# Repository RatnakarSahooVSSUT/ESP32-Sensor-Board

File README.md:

# ESP32-Sensor-Board

> A custom ESP32-C3 based sensor and embedded systems development board designed in KiCad 9.

<p align="center">
  <b>Custom ESP32-C3 Sensor & Embedded Systems Development Board</b>
</p>

---

## 📌 Overview

The **ESP32-Sensor-Board** is a custom embedded systems development board built around the **ESP32-C3** microcontroller.

The board integrates environmental sensing, sound sensing, USB connectivity, battery charging, power regulation, user-interface controls, and external expansion interfaces into a single compact PCB.

The complete hardware design was developed in **KiCad 9**, including schematic capture, hierarchical design, PCB layout, 3D visualization, custom libraries, DFM analysis, and manufacturing outputs.

---

## ✨ Key Features

- 🧠 ESP32-C3 based processing
- 🌡️ BME280 environmental sensor
- 🔊 On-board sound sensing
- 🔌 USB connectivity
- 🔋 Li-ion/Li-Po battery charging
- ⚡ On-board voltage regulation
- 💡 Power and charging indicators
- 🔘 Boot and reset buttons
- 📡 I2C interface
- 🚀 SPI interface
- 🔗 GPIO expansion
- 🧪 Dedicated test points
- 📦 Custom KiCad symbol and footprint libraries
- 🏭 Manufacturing-ready Gerber and drill files
- 📐 Hierarchical schematic design

---

# 🧩 Hardware Overview

| Component / Feature | Description |
|---|---|
| Microcontroller | ESP32-C3 |
| Environmental Sensor | BME280 |
| Sound Sensing | On-board sound sensing circuit |
| USB | USB connectivity |
| Power Input | USB / Rechargeable Battery |
| Battery Charging | Li-ion/Li-Po charging circuit |
| Regulation | On-board voltage regulation |
| Communication | I2C / SPI |
| Expansion | GPIO headers |
| Debugging | Test points |
| PCB Design | KiCad 9 |

---

# 📐 Schematic

The design follows a **hierarchical schematic structure**, separating the major functional blocks into dedicated schematic sheets.

## Complete Schematic

---

# 🌡️ Sensor Section

The sensor subsystem includes the **BME280 environmental sensor**.

### BME280

The BME280 provides digital measurements of:

- Temperature
- Relative Humidity
- Atmospheric Pressure

The sensor communicates with the ESP32-C3 through a digital interface.

### 🔊 Sound Sensing

An on-board sound sensing circuit is also included for detecting variations in ambient sound.

Potential applications include:

- Environmental monitoring
- Sound/activity detection
- IoT sensing
- Event-triggered applications

---

# ⚡ Power Management

The power subsystem manages the board's power input, battery charging, voltage regulation, and status indication.

The design includes:

- USB power input
- Rechargeable battery support
- Battery charging
- Voltage regulation
- Power-status indication
- Charging-status indication

---

# 🎛️ User Interface

The board provides several controls and indicators for development, debugging, and normal operation.

### User Interface Features

- Boot button
- Reset button
- Power indicator
- Charging indicators
- USB RX/TX indicators
- Status indicators

---

# 🖥️ PCB Design

The PCB was designed using **KiCad 9** with emphasis on:

- Compact component placement
- Organized routing
- Functional block separation
- Practical power distribution
- Accessible debugging points
- Clear silkscreen labeling
- External expansion
- Manufacturability

## PCB Layout

## 3D PCB View

---

# 🔌 Interfaces

## USB

USB connectivity is provided for:

- Power
- Programming
- Serial communication

## I2C

The I2C interface allows additional sensors and peripherals to be connected to the board.

## SPI

SPI connectivity is available for peripherals requiring higher-speed communication, such as displays, memory devices, and other external modules.

## GPIO

Additional GPIO pins are exposed through board headers for connecting external sensors, modules, and other peripherals.

---

# 🧪 Debugging & Test Points

Dedicated test points are provided across the board to make hardware bring-up, debugging, and signal verification easier.

These can be used with a:

- Multimeter
- Oscilloscope
- Logic analyzer
- Other debugging equipment

---

# 🏭 Manufacturing

Manufacturing files are provided in the:

**`ESP32_Gerbers/`**

directory.

The repository contains the generated **Gerber and drill files** required for PCB fabrication.

DFM-related manufacturing files are also included under:

**`dfm/gerber/`**

---

# 📁 Repository Structure

    ESP32-Sensor-Board/
    │
    ├── ESP32_Gerbers/
    │   └── Gerber & drill files
    │
    ├── Libraries/
    │   └── Custom KiCad symbols & footprints
    │
    ├── dfm/
    │   └── gerber/
    │       └── DFM / manufacturing files
    │
    ├── images/
    │   ├── ESP32-Schematic.png
    │   ├── PCB-3d-front.png
    │   ├── PCB-layout.png
    │   ├── Power-section-Schematic.png
    │   ├── Sensor-Section.png
    │   └── User-interface.png
    │
    ├── KiCad 9 Esp32 Project.kicad_pro
    ├── KiCad 9 Esp32 Project.kicad_sch
    ├── KiCad 9 Esp32 Project.kicad_pcb
    │
    ├── esp32-c3-02.kicad_sch
    ├── sensors.kicad_sch
    ├── user_interface.kicad_sch
    │
    ├── .gitignore
    └── README.md

---

# 🛠️ Tools & Technologies

- **KiCad 9**
- **ESP32-C3**
- PCB Design
- Schematic Capture
- Hierarchical Schematics
- Embedded Systems
- Sensor Interfaces
- Power Electronics
- IoT Hardware Design
- PCB Manufacturing

---

# ✅ Project Status

| Design Stage | Status |
|---|---|
| Schematic Design | ✅ Completed |
| Hierarchical Schematic | ✅ Completed |
| Sensor Integration | ✅ Completed |
| Power Management | ✅ Completed |
| PCB Layout | ✅ Completed |
| 3D PCB Design | ✅ Completed |
| Custom Libraries | ✅ Completed |
| Gerber Generation | ✅ Completed |
| DFM Analysis | ✅ Completed |
| Hardware Fabrication | 🔄 To be updated |

---

# 📚 Design Files

The complete KiCad project files are included in this repository.

The project can be opened and further modified using **KiCad 9**.

The repository includes:

- KiCad project configuration
- Main hierarchical schematic
- Individual schematic sheets
- PCB layout
- Custom symbol libraries
- Custom footprint libraries
- Gerber files
- Drill files
- DFM outputs
- Project documentation

---

# 👤 Author

**Ratnakar Sahoo**

Embedded Systems & PCB Design

---

# 📄 License

This project is provided for educational and development purposes.

Please refer to the repository contents for the applicable design and manufacturing files.

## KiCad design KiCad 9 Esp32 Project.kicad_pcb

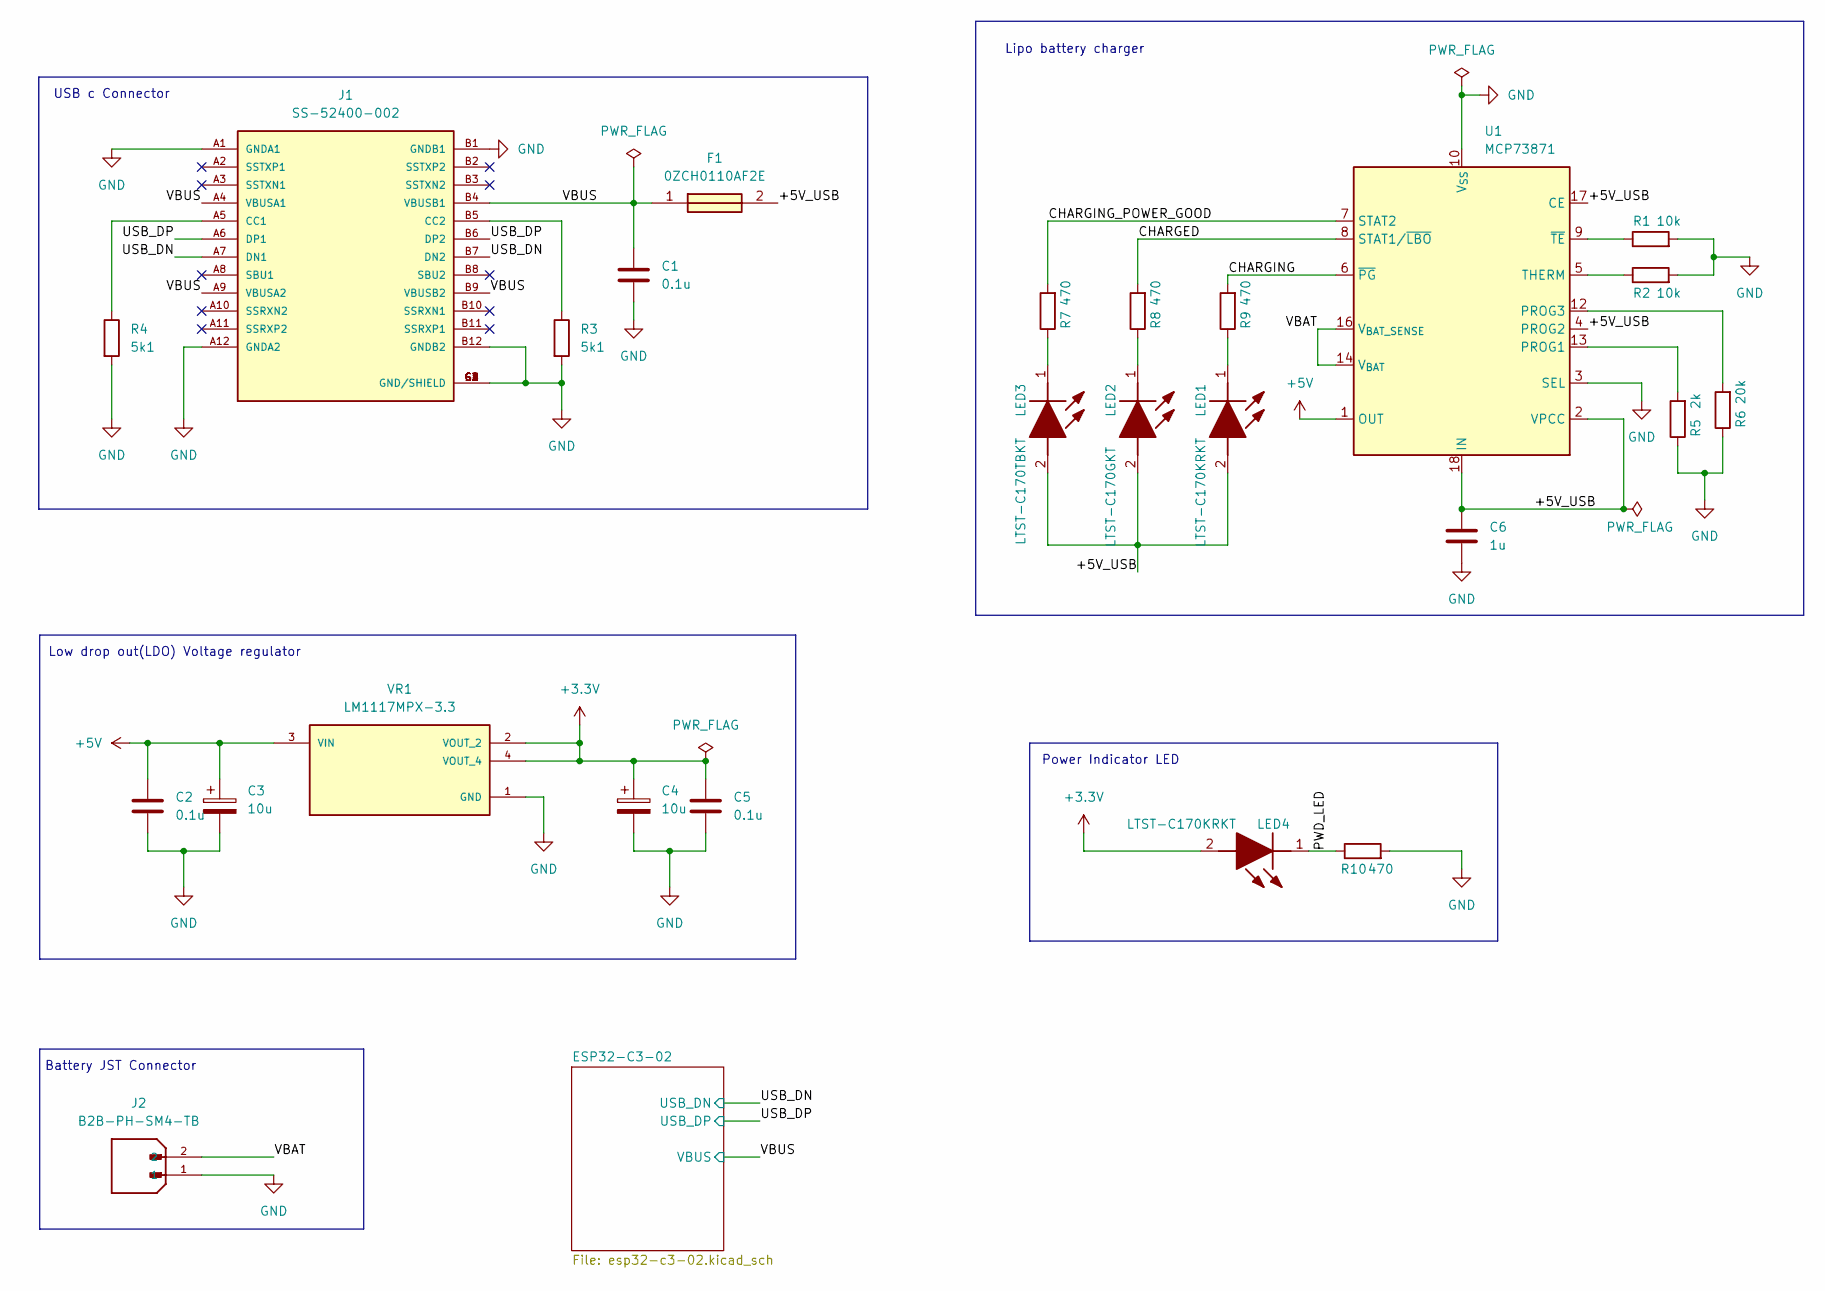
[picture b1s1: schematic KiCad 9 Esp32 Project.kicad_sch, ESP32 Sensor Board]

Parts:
C1, C2, C5: 0.1u; C_0805_2012Metric
C3, C4: 10u; T491A
C6: 1u; C_0805_2012Metric
F1: 0ZCH0110AF2E; FUSC3226X100N; Manufacturer_Part_Number 0ZCH0110AF2E
J1: SS-52400-002; BELFUSE_SS-52400-002; PARTREV A0
J2: B2B-PH-SM4-TB; JST_B2B-PH-SM4-TB; PARTREV N/A
LED1, LED4: LTST-C170KRKT; LEDC2012X120N; Manufacturer_Part_Number LTST-C170KRKT; Mouser Part Number 859-LTST-C170KRKT
LED2: LTST-C170GKT; LEDC2012X120N; Manufacturer_Part_Number LTST-C170GKT; Mouser Part Number 859-LTST-C170GKT
LED3: LTST-C170TBKT; LEDC2012X120N; Manufacturer_Part_Number LTST-C170TBKT; Mouser Part Number 859-LTST-C170TBKT
R1, R2: 10k; R_0805_2012Metric
R3, R4: 5k1; R_0805_2012Metric
R5: 2k; R_0805_2012Metric
R6: 20k; R_0805_2012Metric
R7, R8, R9, R10: 470; R_0805_2012Metric
U1: MCP73871; QFN-20-1EP_4x4mm_P0.5mm_EP2.5x2.5mm
VR1: LM1117MPX-3.3; VREG_LM1117MPX-3.3

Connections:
+3.3V: C4.1, C5.1, LED4.2 (A), VR1.2 (VOUT_2), VR1.4 (VOUT_4); also elsewhere on the board
+5V: C2.1, C3.1, U1.1 (OUT), U1.20 (OUT), VR1.3 (VIN)
/+5V_USB: C6.1, F1.2, LED1.2 (A), LED2.2 (A), LED3.2 (A), U1.2 (VPCC), U1.4 (PROG2), U1.17 (CE), U1.18 (IN), U1.19 (IN)
/CHARGED: R8.2, U1.8 (STAT1/~LBO)
/CHARGING: R9.2, U1.6 (~PG)
/CHARGING_POWER_GOOD: R7.2, U1.7 (STAT2)
/PWD_LED: LED4.1 (K), R10.1
/USB_DN: J1.A7 (DN1), J1.B7 (DN2); also elsewhere on the board
/USB_DP: J1.A6 (DP1), J1.B6 (DP2); also elsewhere on the board
/VBAT: J2.2, U1.14 (V_{BAT}), U1.15 (V_{BAT}), U1.16 (V_{BAT_SENSE})
/VBUS: C1.1, F1.1, J1.A4 (VBUSA1), J1.A9 (VBUSA2), J1.B4 (VBUSB1), J1.B9 (VBUSB2); also elsewhere on the board
GND: C1.2, C2.2, C3.2, C4.2, C5.2, C6.2, J1.A1 (GNDA1), J1.A12 (GNDA2), J1.B1 (GNDB1), J1.B12 (GNDB2), J1.G1 (GND/SHIELD), J1.G2 (GND/SHIELD), J1.G3 (GND/SHIELD), J1.G4 (GND/SHIELD), J1.S1 (GND/SHIELD), J1.S2 (GND/SHIELD), J1.S3 (GND/SHIELD), J1.S4 (GND/SHIELD), J2.1, R1.2, R2.2, R3.2, R4.2, R5.1, R6.1, R10.2, U1.3 (SEL), U1.10 (V_{SS}), U1.11 (V_{SS}), U1.21 (V_{SS}), VR1.1 (GND); also elsewhere on the board
unnamed: J1.A5 (CC1), R4.1
unnamed: J1.B5 (CC2), R3.1
unnamed: LED1.1 (K), R9.1
unnamed: LED2.1 (K), R8.1
unnamed: LED3.1 (K), R7.1
unnamed: R5.2, U1.13 (PROG1)
unnamed: R6.2, U1.12 (PROG3)
unnamed: R2.1, U1.5 (THERM)
unnamed: R1.1, U1.9 (~TE)

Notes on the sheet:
USB c Connector
Low drop out(LDO) Voltage regulator
Battery JST Connector
Power Indicator LED
Lipo battery charger

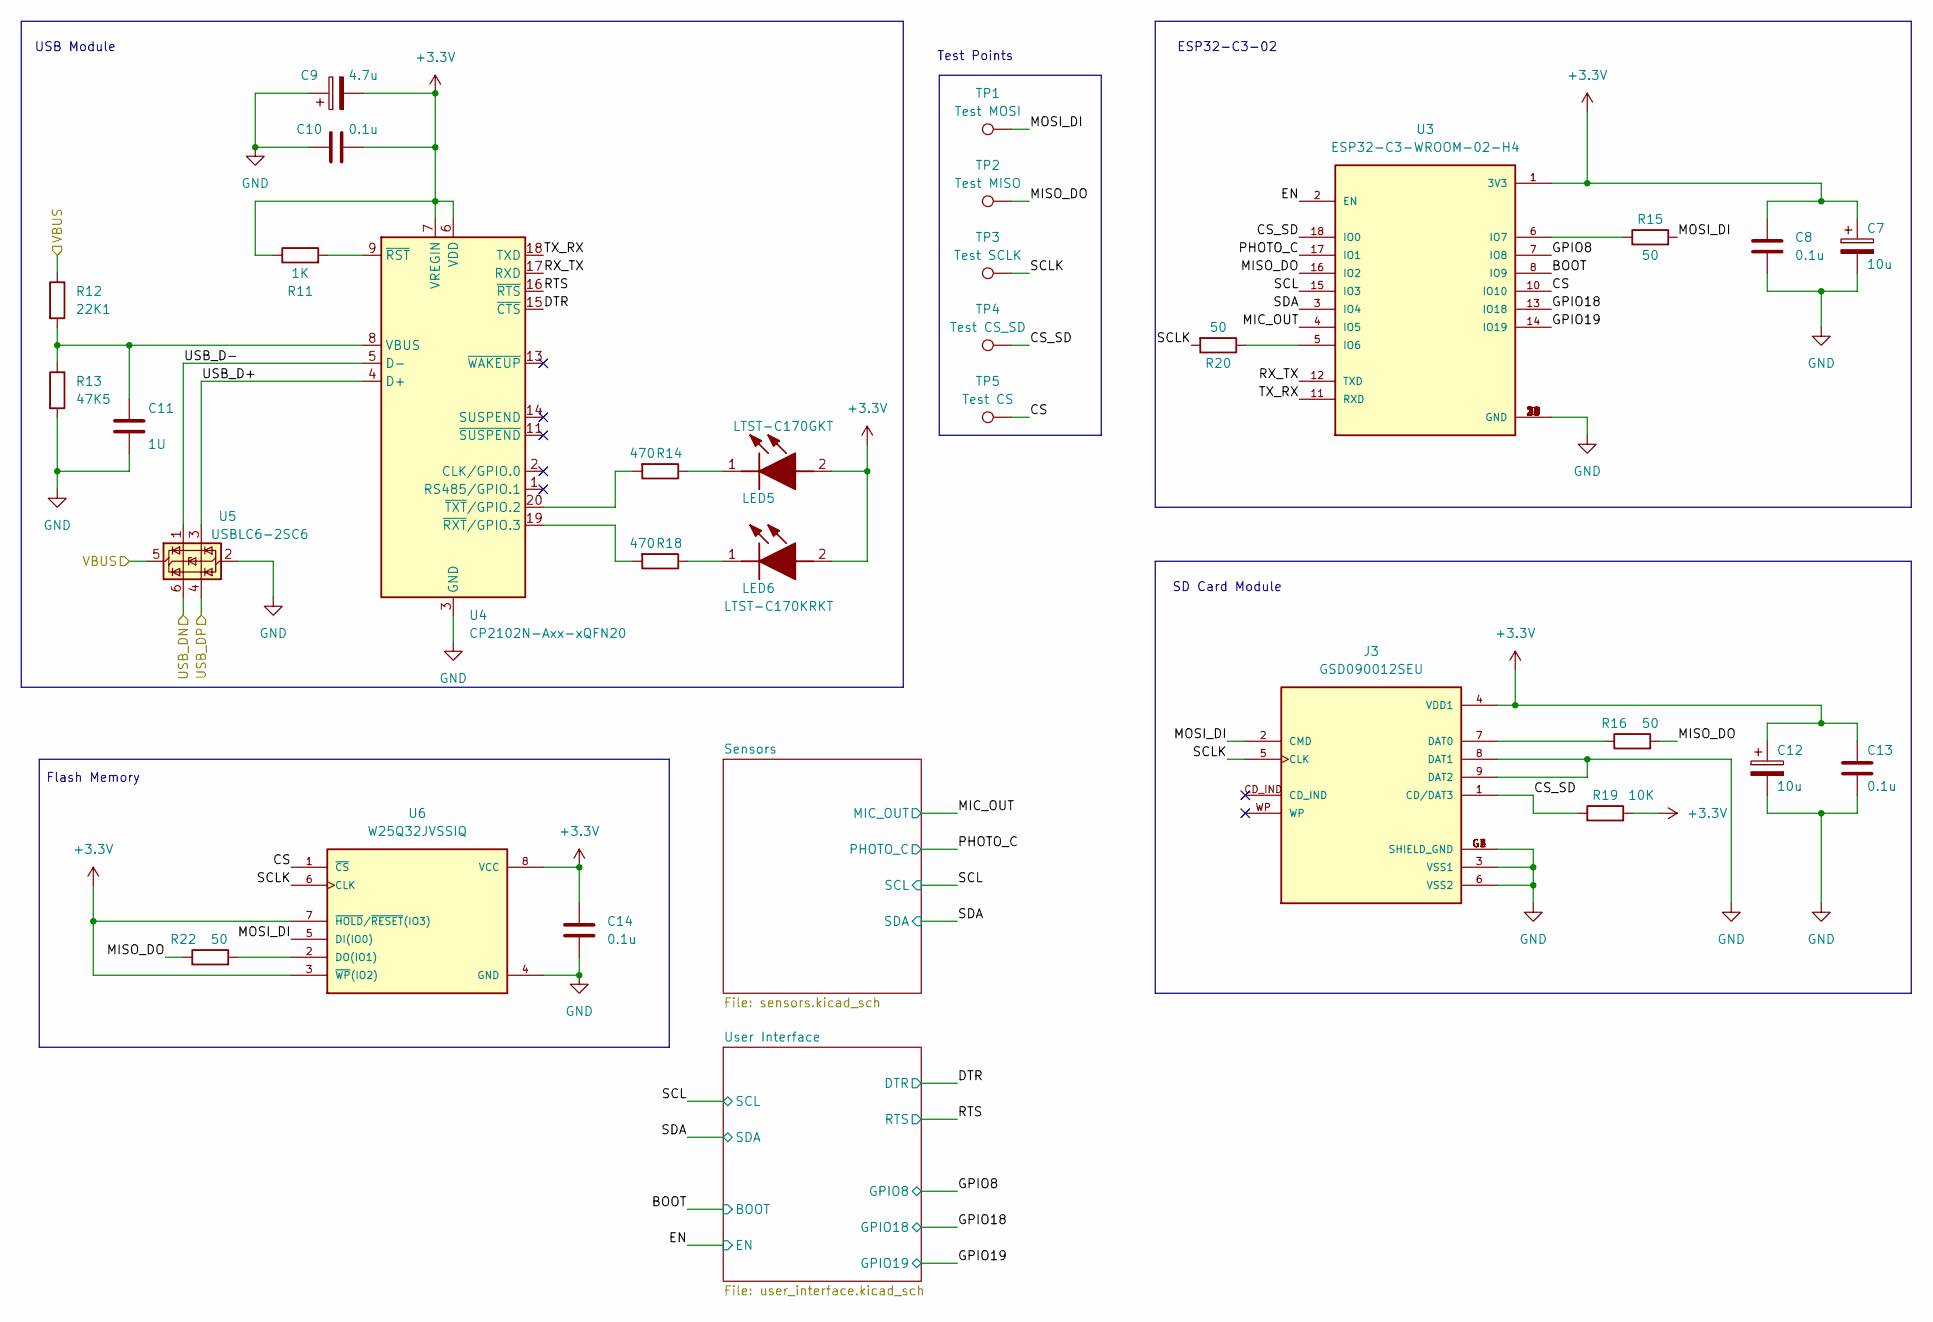
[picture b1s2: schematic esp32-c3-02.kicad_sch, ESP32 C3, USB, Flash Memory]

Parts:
C7, C12: 10u; T491A
C8, C10, C13, C14: 0.1u; C_0805_2012Metric
C9: 4.7u; T491A
C11: 1U; C_0805_2012Metric
J3: GSD090012SEU; AMPHENOL_GSD090012SEU; PARTREV E
LED5: LTST-C170GKT; LEDC2012X120N; Manufacturer_Part_Number LTST-C170GKT; Mouser Part Number 859-LTST-C170GKT
LED6: LTST-C170KRKT; LEDC2012X120N; Manufacturer_Part_Number LTST-C170KRKT; Mouser Part Number 859-LTST-C170KRKT
R11: 1K; R_0805_2012Metric
R12: 22K1; R_0805_2012Metric
R13: 47K5; R_0805_2012Metric
R14, R18: 470; R_0805_2012Metric
R15, R16, R20, R22: 50; R_0805_2012Metric
R19: 10K; R_0805_2012Metric
TP1: Test MOSI; TestPoint_Pad_D1.0mm
TP2: Test MISO; TestPoint_Pad_D1.0mm
TP3: Test SCLK; TestPoint_Pad_D1.0mm
TP4: Test CS_SD; TestPoint_Pad_D1.0mm
TP5: Test CS; TestPoint_Pad_D1.0mm
U3: ESP32-C3-WROOM-02-H4; MODULE_ESP32-C3-WROOM-02-H4
U4: CP2102N-Axx-xQFN20; SiliconLabs_QFN-20-1EP_3x3mm_P0.5mm_EP1.8x1.8mm
U5: USBLC6-2SC6; SOT-23-6
U6: W25Q32JVSSIQ; SOIC127P790X216-8N; M_PART_NUMBER W25QXX

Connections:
+3.3V: C7.1, C8.2, C9.2, C10.2, C12.1, C13.2, C14.2, J3.4 (VDD1), LED5.2 (A), LED6.2 (A), R11.1, R19.2, U3.1 (3V3), U4.6 (VDD), U4.7 (VREGIN), U6.3 (~WP(IO2)), U6.7 (~HOLD/~RESET(IO3)), U6.8 (VCC); also elsewhere on the board
/ESP32-C3-02/BOOT: U3.8 (IO9); also elsewhere on the board
/ESP32-C3-02/CS: TP5.1, U3.10 (IO10), U6.1 (~CS)
/ESP32-C3-02/CS_SD: J3.1 (CD/DAT3), R19.1, TP4.1, U3.18 (IO0)
/ESP32-C3-02/DTR: U4.15 (~CTS); also elsewhere on the board
/ESP32-C3-02/EN: U3.2 (EN); also elsewhere on the board
/ESP32-C3-02/GPIO8: U3.7 (IO8); also elsewhere on the board
/ESP32-C3-02/GPIO18: U3.13 (IO18); also elsewhere on the board
/ESP32-C3-02/GPIO19: U3.14 (IO19); also elsewhere on the board
/ESP32-C3-02/MIC_OUT: U3.4 (IO5); also elsewhere on the board
/ESP32-C3-02/MISO_DO: R16.2, R22.1, TP2.1, U3.16 (IO2)
/ESP32-C3-02/MOSI_DI: J3.2 (CMD), R15.2, TP1.1, U6.5 (DI(IO0))
/ESP32-C3-02/PHOTO_C: U3.17 (IO1); also elsewhere on the board
/ESP32-C3-02/RTS: U4.16 (~RTS); also elsewhere on the board
/ESP32-C3-02/RX_TX: U3.12 (TXD), U4.17 (RXD)
/ESP32-C3-02/SCL: U3.15 (IO3); also elsewhere on the board
/ESP32-C3-02/SCLK: J3.5 (CLK), R20.2, TP3.1, U6.6 (CLK)
/ESP32-C3-02/SDA: U3.3 (IO4); also elsewhere on the board
/ESP32-C3-02/TX_RX: U3.11 (RXD), U4.18 (TXD)
/ESP32-C3-02/USB_D+: U4.4 (D+), U5.3 (I/O2)
/ESP32-C3-02/USB_D-: U4.5 (D-), U5.1 (I/O1)
/USB_DN: U5.6 (I/O1); also elsewhere on the board
/USB_DP: U5.4 (I/O2); also elsewhere on the board
/VBUS: R12.1, U5.5 (VBUS); also elsewhere on the board
GND: C7.2, C8.1, C9.1, C10.1, C11.2, C12.2, C13.1, C14.1, J3.3 (VSS1), J3.6 (VSS2), J3.8 (DAT1), J3.9 (DAT2), J3.G1 (SHIELD_GND), J3.G2 (SHIELD_GND), J3.G3 (SHIELD_GND), J3.G4 (SHIELD_GND), R13.2, U3.9 (GND), U3.19 (GND), U3.20 (GND), U3.21 (GND), U3.22 (GND), U3.23 (GND), U3.24 (GND), U3.25 (GND), U3.26 (GND), U3.27 (GND), U3.28 (GND), U3.29 (GND), U3.30 (GND), U3.31 (GND), U3.32 (GND), U3.33 (GND), U3.34 (GND), U3.35 (GND), U3.36 (GND), U3.37 (GND), U3.38 (GND), U3.39 (GND), U4.3 (GND), U4.12 (GND), U4.21 (GND), U5.2 (GND), U6.4 (GND); also elsewhere on the board
unnamed: J3.7 (DAT0), R16.1
unnamed: LED5.1 (K), R14.1
unnamed: LED6.1 (K), R18.1
unnamed: R20.1, U3.5 (IO6)
unnamed: R15.1, U3.6 (IO7)
unnamed: C11.1, R12.2, R13.1, U4.8 (VBUS)
unnamed: R11.2, U4.9 (~RST)
unnamed: R18.2, U4.19 (~RXT/GPIO.3)
unnamed: R14.2, U4.20 (~TXT/GPIO.2)
unnamed: R22.2, U6.2 (DO(IO1))

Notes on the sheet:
Flash Memory
Test Points
ESP32-C3-02
SD Card Module
USB Module

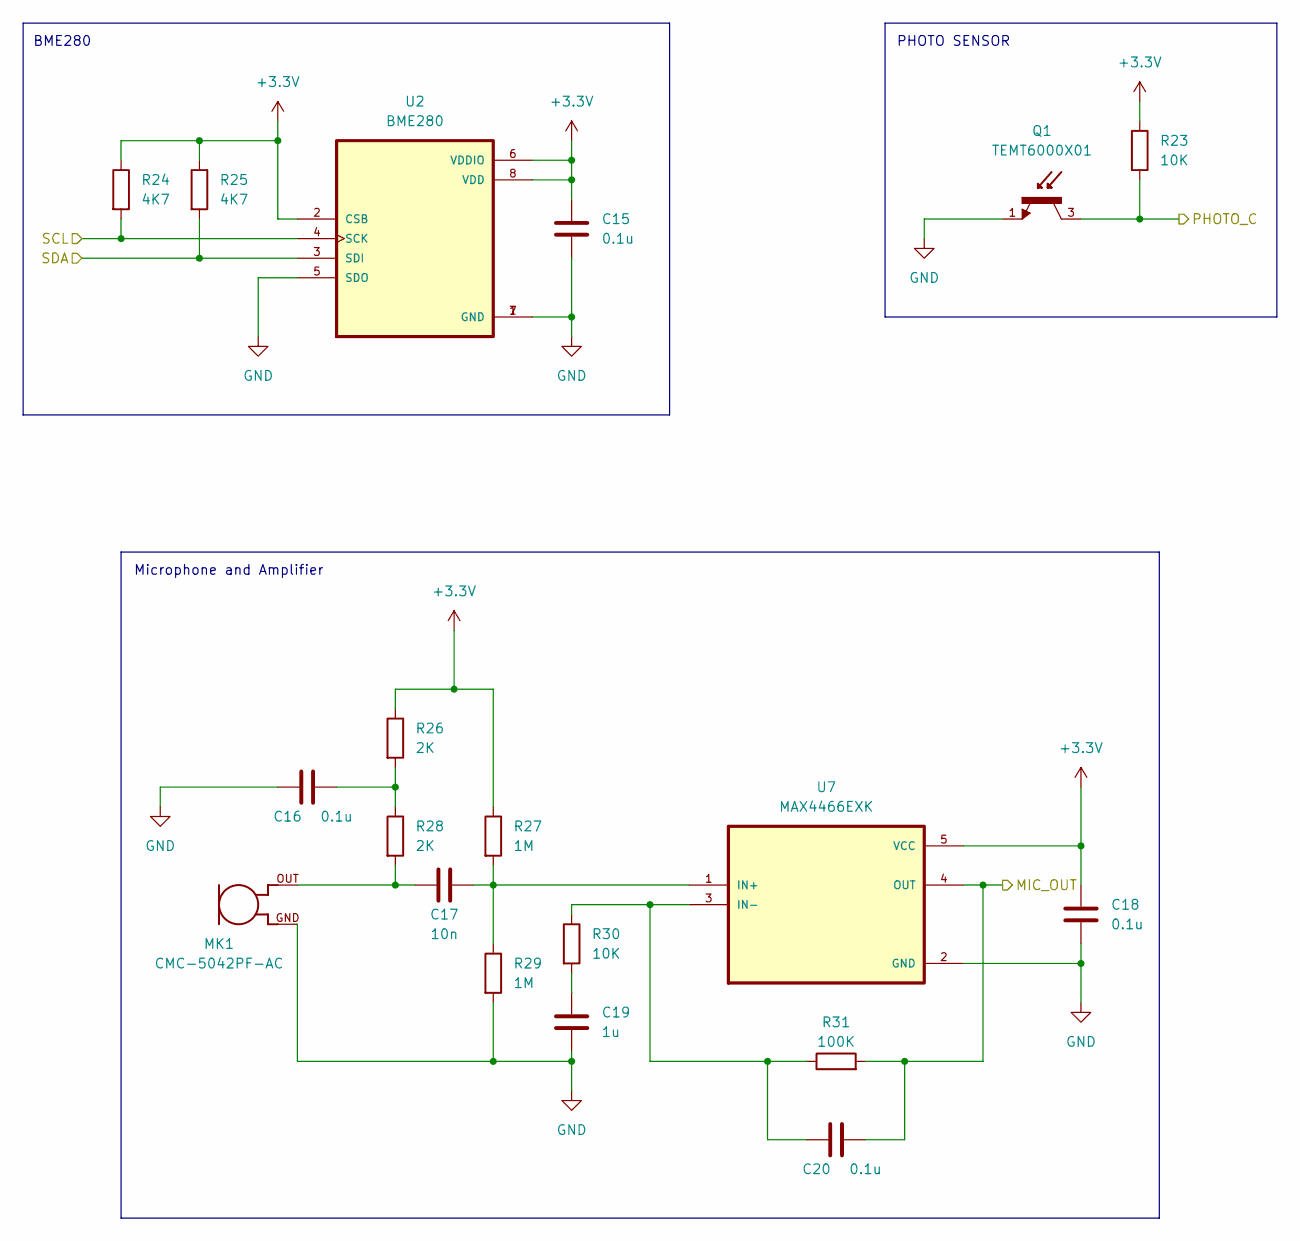
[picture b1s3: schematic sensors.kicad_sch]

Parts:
C15, C16, C18, C20: 0.1u; C_0805_2012Metric
C17: 10n; C_0805_2012Metric
C19: 1u; C_0805_2012Metric
MK1: CMC-5042PF-AC; CUI_CMC-5042PF-AC
Q1: TEMT6000X01; TRANS_TEMT6000X01; PARTREV 1.9
R23, R30: 10K; R_0805_2012Metric
R24, R25: 4K7; R_0805_2012Metric
R26, R28: 2K; R_0805_2012Metric
R27, R29: 1M; R_0805_2012Metric
R31: 100K; R_0805_2012Metric
U2: BME280; PSON65P250X250X100-8N
U7: MAX4466EXK; SOT65P210X110-5N

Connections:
+3.3V: C15.1, C18.1, R23.1, R24.1, R25.1, R26.1, R27.1, U2.2 (CSB), U2.6 (VDDIO), U2.8 (VDD), U7.5 (VCC); also elsewhere on the board
/ESP32-C3-02/MIC_OUT: C20.2, R31.2, U7.4 (OUT); also elsewhere on the board
/ESP32-C3-02/PHOTO_C: Q1.3, R23.2; also elsewhere on the board
/ESP32-C3-02/SCL: R24.2, U2.4 (SCK); also elsewhere on the board
/ESP32-C3-02/SDA: R25.2, U2.3 (SDI); also elsewhere on the board
GND: C15.2, C16.1, C18.2, C19.2, MK1.GND, Q1.1, R29.2, U2.1 (GND), U2.5 (SDO), U2.7 (GND), U7.2 (GND); also elsewhere on the board
unnamed: C16.2, R26.2, R28.1
unnamed: C17.1, MK1.OUT, R28.2
unnamed: C19.1, R30.2
unnamed: C17.2, R27.2, R29.1, U7.1 (IN+)
unnamed: C20.1, R30.1, R31.1, U7.3 (IN-)

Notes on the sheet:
PHOTO SENSOR
BME280
Microphone and Amplifier

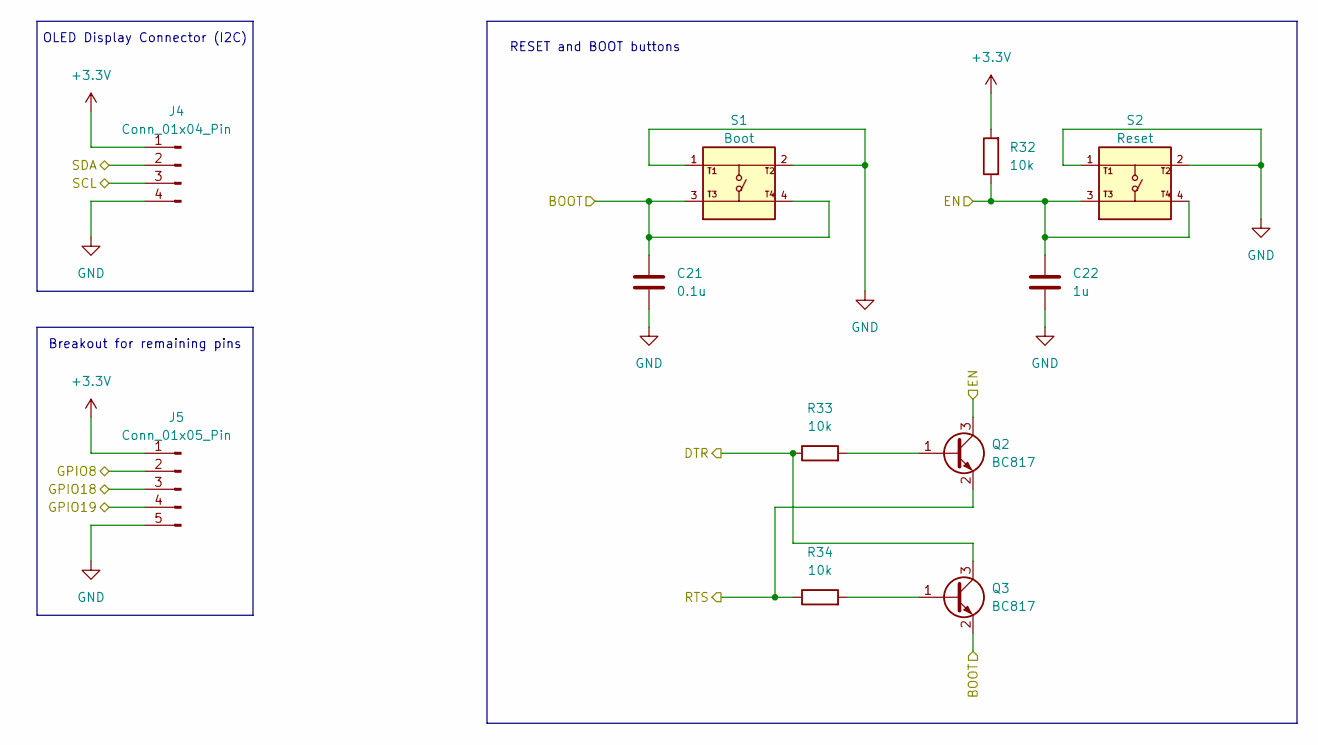
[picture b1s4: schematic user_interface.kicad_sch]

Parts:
C21: 0.1u; C_0805_2012Metric
C22: 1u; C_0805_2012Metric
J4: Conn_01x04_Pin; PinSocket_1x04_P2.54mm_Vertical
J5: Conn_01x05_Pin; PinSocket_1x05_P2.54mm_Vertical
Q2, Q3: BC817; SOT-23
R32, R33, R34: 10k; R_0805_2012Metric
S1: Boot; SW_USLPT2819DT2TR; PARTREV P
S2: Reset; SW_USLPT2819DT2TR; PARTREV P

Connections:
+3.3V: J4.1, J5.1, R32.2; also elsewhere on the board
/ESP32-C3-02/BOOT: C21.1, Q3.2 (E), S1.3, S1.4; also elsewhere on the board
/ESP32-C3-02/DTR: Q3.3 (C), R33.1; also elsewhere on the board
/ESP32-C3-02/EN: C22.1, Q2.3 (C), R32.1, S2.3, S2.4; also elsewhere on the board
/ESP32-C3-02/GPIO8: J5.2; also elsewhere on the board
/ESP32-C3-02/GPIO18: J5.3; also elsewhere on the board
/ESP32-C3-02/GPIO19: J5.4; also elsewhere on the board
/ESP32-C3-02/RTS: Q2.2 (E), R34.1; also elsewhere on the board
/ESP32-C3-02/SCL: J4.3; also elsewhere on the board
/ESP32-C3-02/SDA: J4.2; also elsewhere on the board
GND: C21.2, C22.2, J4.4, J5.5, S1.1, S1.2, S2.1, S2.2; also elsewhere on the board
unnamed: Q2.1 (B), R33.2
unnamed: Q3.1 (B), R34.2

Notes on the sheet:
RESET and BOOT buttons
OLED Display Connector (I2C)
Breakout for remaining pins

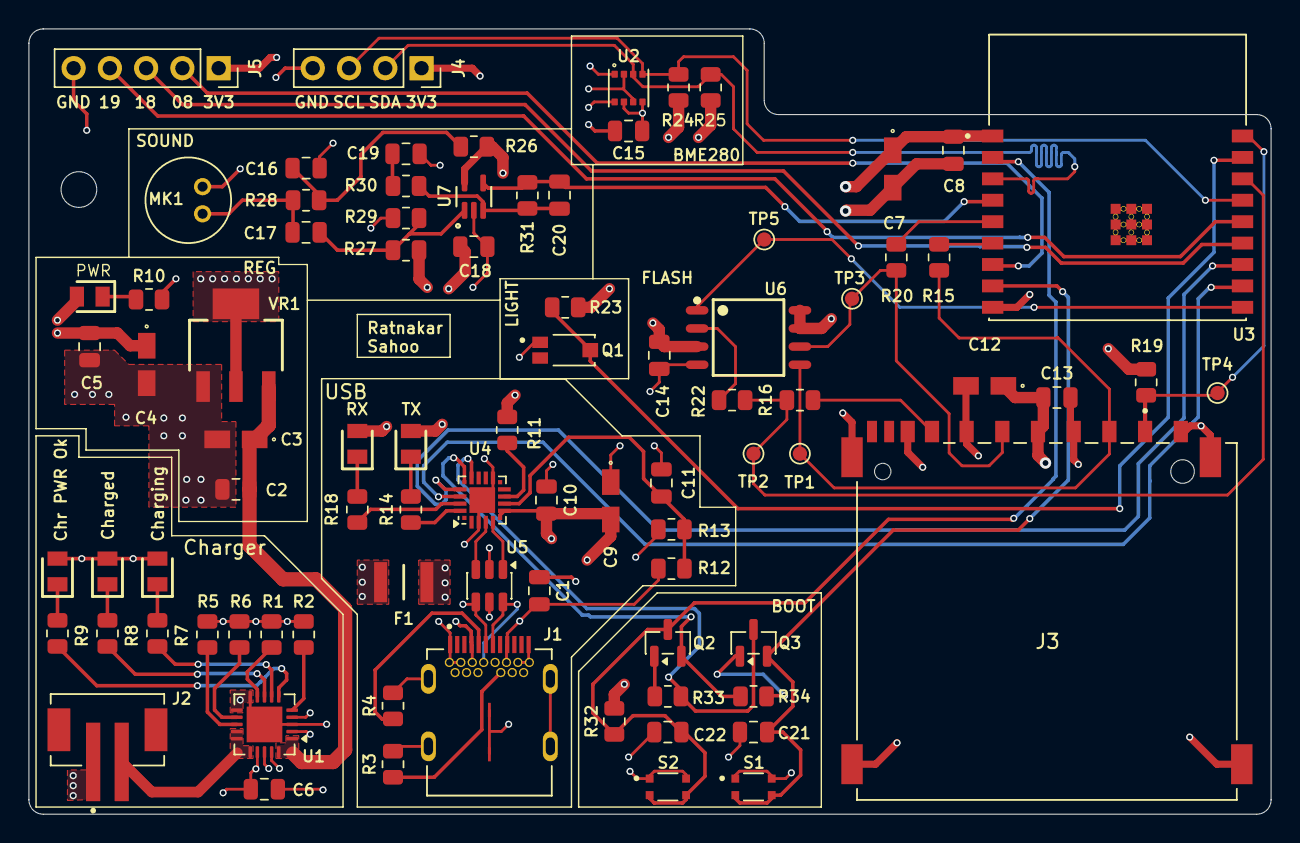
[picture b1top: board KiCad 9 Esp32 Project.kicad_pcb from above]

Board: 4 copper layers, 87.0 x 55.0 mm, 85 parts (0 on the bottom side), 58 nets.
